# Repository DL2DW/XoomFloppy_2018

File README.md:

# XoomFloppy - Elegant XUM1541 version

## Introduction

The XUM1541 is an adapter that allows Commodore peripherals, such as floppy drives and printers, to be connected to a PC via USB. So you can easily read or write floppy disks from a PC to a 1541. 

The ZoomFloppy is a commercial and very well known version of the XUM1541, which offers some other advantages.

The ZoomFloppy has become a de facto standard, especially concerning the firmware. 

For some applications, for example when I only need the IEC bus, the ZoomFloppy is just too big, so I developed a miniature version of the ZoomFloppy. The result is the XoomFloppy, a 100% compatible clone, running the original firmware of the ZoomFloppy.

# Technical

I basically just shrunk the ZoomFloppy. This, of course, eliminated the IEEE-488 and parallel port.

But the hardware base is otherwise the same. This makes the XoomFloppy the only other device that is 100% compatible. 

The core is the ATmega32u2, on which the original firmware of the ZoomFloppy is flashed. But also the driver module 7406 is present.

In the Docs folder I put a manual in German, which explains the assembly and the subsequent installation of the firmware.

# Case

From the company [Richard Wöhr GmbH](http://www.woehrgmbh.de/) there is a small USB case in which my board fits perfectly. So you can also upgrade the whole thing very elegant. And the electronics are very well protected.

The order number for the transparent version shown here is: [GH02SG001](https://www.industriegehaeuse.de/fileadmin/pdfs/steckergehaeuse/gh02sg001_verschraubbar_mit_kabelausgang.pdf)

# BOM

The parts list consists of commercially available parts, which should actually be easy to obtain.

|      | Description                                                 | Part          | References          | Value             | Footprint                       | Quantity Per PCB |
| ---- | ----------------------------------------------------------- | ------------- | ------------------- | ----------------- | ------------------------------- | ---------------- |
| 1    | Unpolarized capacitor                                       | C             | C4 C5               | 100nF             | C_0805_2012Metric               | 2                |
| 2    | Unpolarized capacitor                                       | C             | C3                  | 1µF               | C_0805_2012Metric               | 1                |
| 3    | Unpolarized capacitor                                       | C             | C1 C2               | 22pF              | C_0805_2012Metric               | 2                |
| 4    | Light emitting diode                                        | LED           | D1                  | LED Blue          | LED_0805_2012Metric             | 1                |
| 5    | TVS.3 3.5pF [SOT-23-6]                                      | USBLC6-2SC6   | DZ1                 | USBLC6-2SC6       | SOT-23-6                        | 1                |
| 6    | Resettable fuse, polymeric positive temperature coefficient | Polyfuse      | F1                  | Polyfuse 1206L150 | Fuse_1206_3216Metric            | 1                |
| 7    |                                                             | 7406D         | IC1                 | 7406D             | SOIC-14_3.9x8.7mm_P1.27mm       | 1                |
| 8    | USB Type A connector                                        | USB_A         | J2                  | USB_A             | USB_Male_A_UP2-AH-1-TH          | 1                |
| 9    | Resistor                                                    | R             | R2 R4 R6 R8 R10 R11 | 100k              | R_0805_2012Metric               | 6                |
| 10   | Resistor                                                    | R             | R16                 | 10k               | R_0805_2012Metric               | 1                |
| 11   | Resistor                                                    | R             | R12                 | 120               | R_0805_2012Metric               | 1                |
| 12   | Resistor                                                    | R             | R13 R14             | 22                | R_0805_2012Metric               | 2                |
| 13   | Resistor                                                    | R             | R1 R3 R5 R7 R9      | 4k7               | R_0805_2012Metric               | 5                |
| 14   | 16MHz, 32kB Flash, 1kB SRAM, 1kB EEPROM, TQFP-32            | ATmega32U2-AU | U3                  | ATmega32U2-AU     | TQFP-32_7x7mm_P0.8mm            | 1                |
| 15   | Two pin crystal                                             | Crystal       | Y1                  | 16MHz             | Crystal_SMD_5032-2Pin_5.0x3.2mm | 1                |

# PCB

The PCB can either be ordered directly from [PCBWay](https://www.pcbway.com/project/shareproject/XommFloppy___Elegant_XUM1541_version.html), or you can create it yourself from the Gerber files available here.

If you liked my project, I would be very happy about a small coffee donation.

# License

The contents of this repository, with the exception of the Docs and Software directories, are released under the following license:

- the "Creative Commons Attribution-NonCommercial-ShareAlike 4.0 International License" (CC BY-NC-SA 4.0) full text of this license is included in the [LICENSE.CC-NC-BY-SA-4.0](https://github.com/DL2DW/XoomFloppy_2018/blob/main/LICENSE.CC-NC-BY-SA) file and a copy can also be found at https://creativecommons.org/licenses/by-nc-sa/4.0/

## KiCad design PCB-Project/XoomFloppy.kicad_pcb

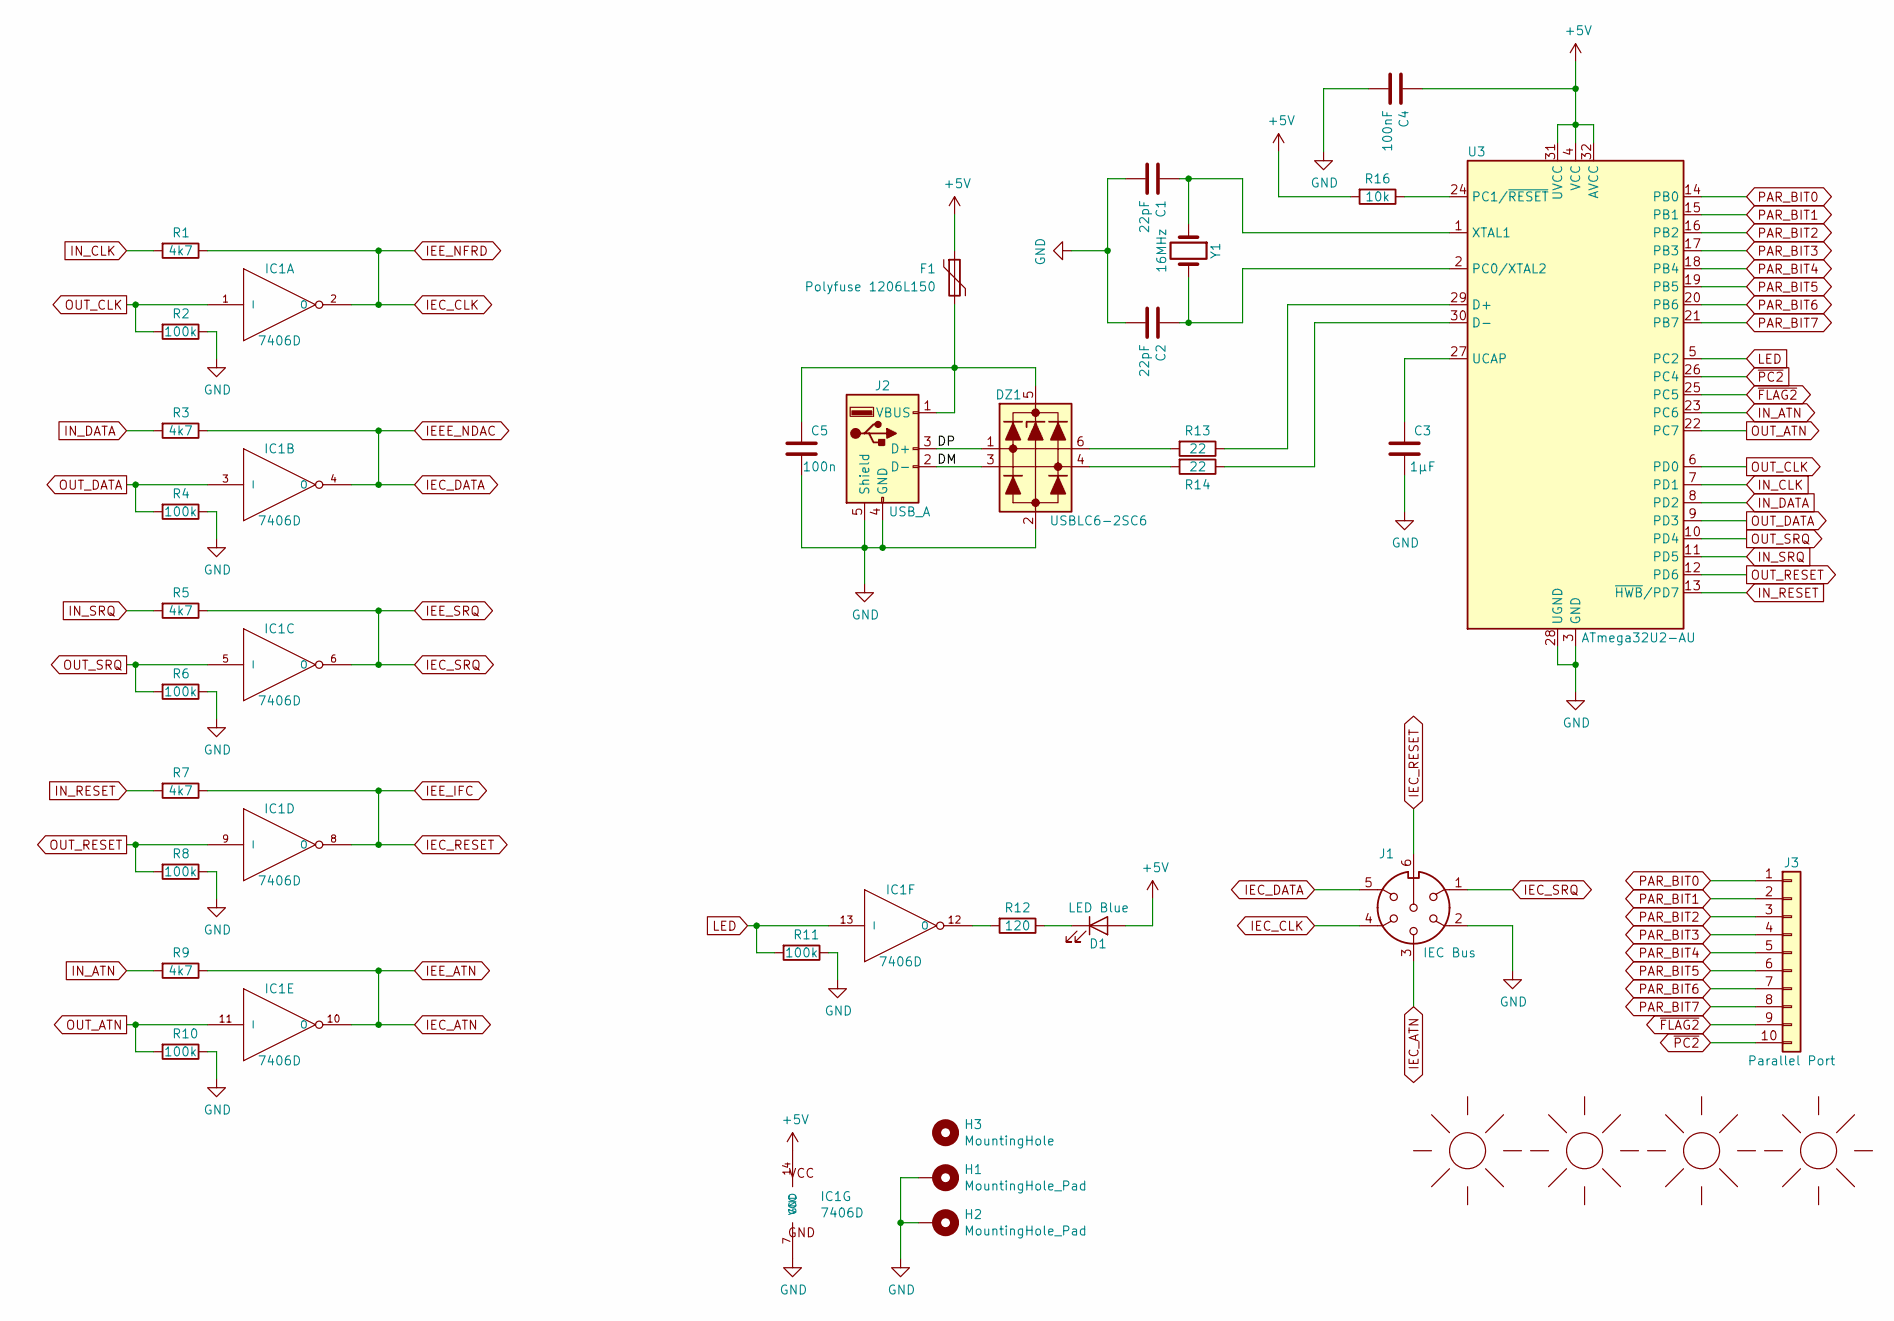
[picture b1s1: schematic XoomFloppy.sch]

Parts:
C1, C2: 22pF; C_0805_2012Metric
C3: 1µF; C_0805_2012Metric
C4: 100nF; C_0805_2012Metric
C5: 100n; C_0805_2012Metric
D1: LED Blue; LED_0805_2012Metric
DZ1: USBLC6-2SC6; SOT-23-6
F1: Polyfuse 1206L150; Fuse_1206_3216Metric
H1, H2: MountingHole_Pad; MountingHole_2.7mm_M2.5_Pad
H3: MountingHole; MountingHole_4mm
IC1: 7406D; SOIC-14_3.9x8.7mm_P1.27mm
J1: IEC Bus; PinHeader_1x06_P2.00mm_Vertical
J2: USB_A; USB_Male_A_UP2-AH-1-TH
J3: Parallel Port; PinHeader_1x10_P1.27mm_Vertical
M1: SUNLOGO; KiCad-Logo2_6mm_SilkScreen
M2: SUNLOGO; Logo_silk_CC-BY-NC-SA_5x2mm
M3: SUNLOGO; Logo_silk_OSHW_6x6mm
M4: SUNLOGO; DL2DW_Logo_Silk_10x5mm
R1, R3, R5, R7, R9: 4k7; R_0805_2012Metric
R2, R4, R6, R8, R10, R11: 100k; R_0805_2012Metric
R12: 120; R_0805_2012Metric
R13, R14: 22; R_0805_2012Metric
R16: 10k; R_0805_2012Metric
U3: ATmega32U2-AU; TQFP-32_7x7mm_P0.8mm
Y1: 16MHz; Crystal_SMD_5032-2Pin_5.0x3.2mm

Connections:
+5V: C4.2, D1.2 (A), F1.1, IC1.14 (VCC), R16.2, U3.4 (VCC), U3.31 (UVCC), U3.32 (AVCC)
/DM: DZ1.3, J2.2 (D-)
/DP: DZ1.1, J2.3 (D+)
GND: C1.2, C2.2, C3.1, C4.1, C5.1, DZ1.2, H1.1, H2.1, IC1.7 (GND), J1.2, J2.4 (GND), J2.5 (Shield), R2.1, R4.1, R6.1, R8.1, R10.1, R11.1, U3.3 (GND), U3.28 (UGND)
IEC_ATN: IC1.10 (O), J1.3, R9.1
IEC_CLK: IC1.2 (O), J1.4, R1.1
IEC_DATA: IC1.4 (O), J1.5, R3.1
IEC_RESET: IC1.8 (O), J1.6, R7.1
IEC_SRQ: IC1.6 (O), J1.1, R5.1
IN_ATN: R9.2, U3.23 (PC6)
IN_CLK: R1.2, U3.7 (PD1)
IN_DATA: R3.2, U3.8 (PD2)
IN_RESET: R7.2, U3.13 (~HWB~/PD7)
IN_SRQ: R5.2, U3.11 (PD5)
LED: IC1.13 (I), R11.2, U3.5 (PC2)
unnamed: C1.1, U3.1 (XTAL1), Y1.1
unnamed: C2.1, U3.2 (PC0/XTAL2), Y1.2
unnamed: C3.2, U3.27 (UCAP)
unnamed: C5.2, DZ1.5, F1.2, J2.1 (VBUS)
unnamed: D1.1 (K), R12.1
unnamed: DZ1.4, R14.2
unnamed: DZ1.6, R13.2
unnamed: IC1.12 (O), R12.2
unnamed: R13.1, U3.29 (D+)
unnamed: R14.1, U3.30 (D-)
unnamed: R16.1, U3.24 (PC1/~RESET)
OUT_ATN: IC1.11 (I), R10.2, U3.22 (PC7)
OUT_CLK: IC1.1 (I), R2.2, U3.6 (PD0)
OUT_DATA: IC1.3 (I), R4.2, U3.9 (PD3)
OUT_RESET: IC1.9 (I), R8.2, U3.12 (PD6)
OUT_SRQ: IC1.5 (I), R6.2, U3.10 (PD4)
PAR_BIT0: J3.1, U3.14 (PB0)
PAR_BIT1: J3.2, U3.15 (PB1)
PAR_BIT2: J3.3, U3.16 (PB2)
PAR_BIT3: J3.4, U3.17 (PB3)
PAR_BIT4: J3.5, U3.18 (PB4)
PAR_BIT5: J3.6, U3.19 (PB5)
PAR_BIT6: J3.7, U3.20 (PB6)
PAR_BIT7: J3.8, U3.21 (PB7)
~FLAG2: J3.9, U3.25 (PC5)
~PC2: J3.10, U3.26 (PC4)

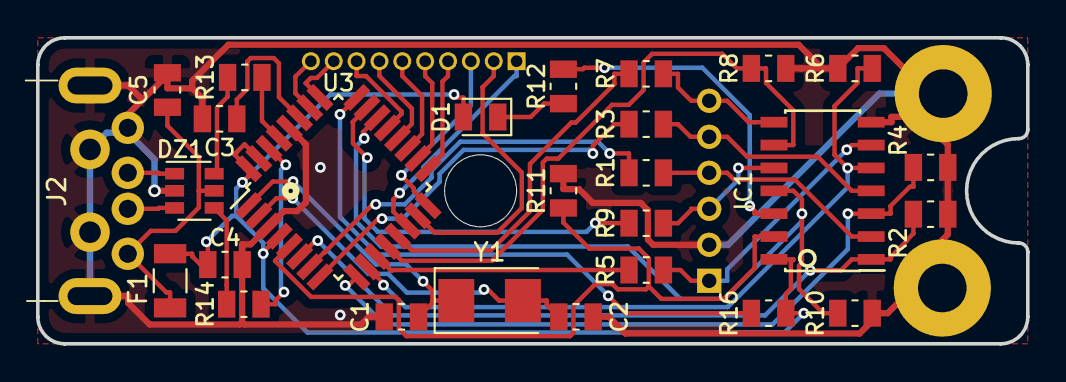
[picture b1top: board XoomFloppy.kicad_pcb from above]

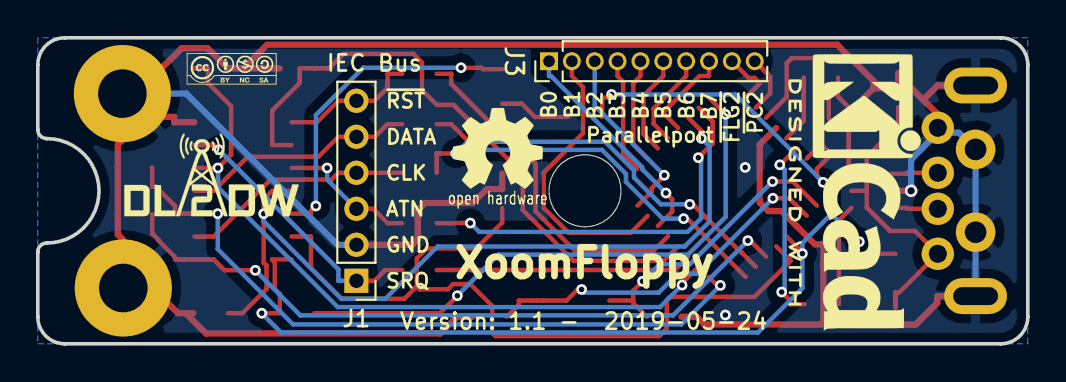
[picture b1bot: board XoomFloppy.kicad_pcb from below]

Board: 2 copper layers, 55.0 x 17.0 mm, 36 parts (6 on the bottom side), 41 nets.

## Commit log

2021-01-06 PCB order link added
